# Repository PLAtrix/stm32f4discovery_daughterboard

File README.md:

This is a Daughterboard for the STM32F4 Discovery for Paparazzi.
Mainly a brakout board for all bus (UART, SPI, I2C...) and PWM outputs.

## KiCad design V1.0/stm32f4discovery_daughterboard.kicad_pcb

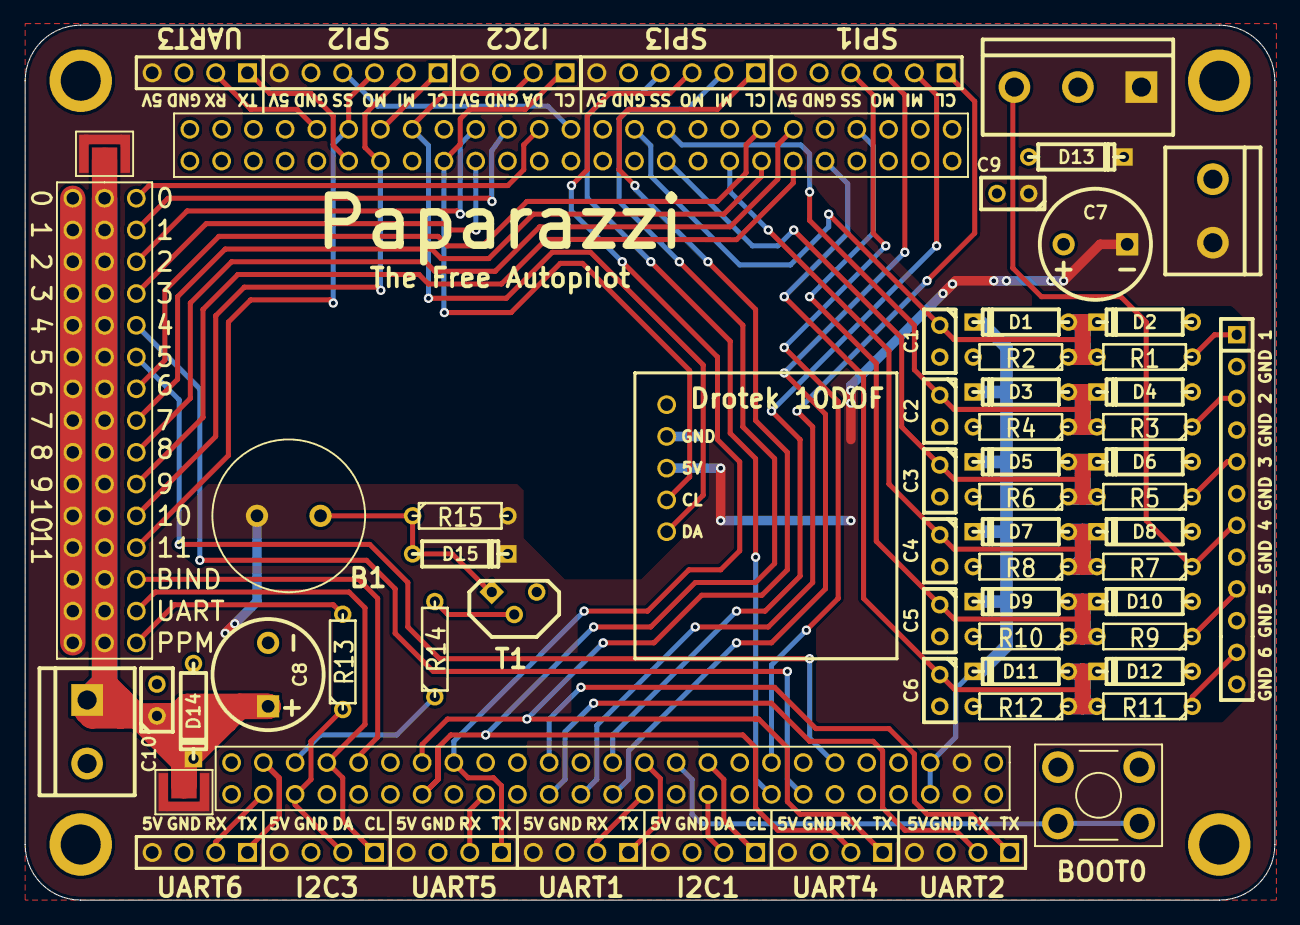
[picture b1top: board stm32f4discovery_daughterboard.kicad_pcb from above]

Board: 2 copper layers, 99.9 x 70.0 mm, 69 parts (0 on the bottom side), 60 nets.

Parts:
3,2mm1, 3,2mm2, 3,2mm3, 3,2mm4: MOUNTING_HOLE; mounting_hole_3,2mm
ADC1: CONN_12; SIL-12
B1: BUZZER_12.2X3.5; buzzer_PS1240P02CT3
BOOT0: SW_PUSH; pushbutton_tactile
C1, C2, C3, C4, C5, C6, C9, C10: 100n; C1
C7, C8: CAPAPOL; C2V8
D1, D2, D3, D4, D5, D6, D7, D8, D9, D10, D11, D12, D13, D14, D15: DIODE; D3
Drotek10DOF1: CONN_5; drotek10dof
I2C1, I2C2, I2C3: CONN_4; PIN_ARRAY_4x1
JP1, JP2: JUMPER; Ujumper
P1, P2: CONN_25X2; pin_array_25x2
PWM/PPM/Spektrum1: CONN_15X3; pin_array_15x3
R1, R3, R5, R7, R9, R11: 22k; R3
R2, R4, R6, R8, R10, R12: 2k2; R3
R13: 220; R3
R14: 470; R3
R15: 1k; R3
SPI1, SPI2, SPI3: CONN_6; PIN_ARRAY-6X1
T1: BC547; TO92
UART1, UART2, UART3, UART4, UART5, UART6: CONN_4; PIN_ARRAY_4x1
screw1: CONN_3; bornier3
screw2, screw3: CONN_2; bornier2

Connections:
3V: D1.2, D3.2, D5.2, D7.2, D9.2, D11.2, P2.5, P2.6
5V: B1.1, C7.1, C9.1, D13.2, D15.2, Drotek10DOF1.3, I2C1.4, I2C2.4, I2C3.4, JP1.1, JP2.1, P2.3, P2.4, R15.2, SPI1.6, SPI2.6, SPI3.6, UART1.4, UART2.4, UART3.4, UART4.4, UART5.4, UART6.4, screw1.1, screw2.1
ADC1: ADC1.1, R1.1
ADC2: ADC1.3, R3.1
ADC3: ADC1.5, R5.1
ADC4: ADC1.7, R7.1, screw1.3
ADC5: ADC1.9, R9.1
ADC6: ADC1.11, R11.1
BOOT0: BOOT0.2, P2.21
GND: 3,2mm1.1, 3,2mm2.1, 3,2mm3.1, 3,2mm4.1, ADC1.2, ADC1.4, ADC1.6, ADC1.8, ADC1.10, ADC1.12, BOOT0.1, C1.2, C2.2, C3.2, C4.2, C5.2, C6.2, C7.2, C8.2, C9.2, C10.2, D2.1, D4.1, D6.1, D8.1, D10.1, D12.1, D13.1, D14.1, Drotek10DOF1.2, I2C1.3, I2C2.3, I2C3.3, P1.1, P1.2, P1.5, P1.23, P1.49, P1.50, P2.1, P2.2, P2.49, P2.50, PWM/PPM/Spektrum1.1, PWM/PPM/Spektrum1.4, PWM/PPM/Spektrum1.7, PWM/PPM/Spektrum1.10, PWM/PPM/Spektrum1.13, PWM/PPM/Spektrum1.16, PWM/PPM/Spektrum1.19, PWM/PPM/Spektrum1.22, PWM/PPM/Spektrum1.25, PWM/PPM/Spektrum1.28, PWM/PPM/Spektrum1.31, PWM/PPM/Spektrum1.34, PWM/PPM/Spektrum1.37, PWM/PPM/Spektrum1.40, PWM/PPM/Spektrum1.43, R2.2, R4.2, R6.2, R8.2, R10.2, R12.2, SPI1.5, SPI2.5, SPI3.5, T1.3, UART1.3, UART2.3, UART3.3, UART4.3, UART5.3, UART6.3, screw1.2, screw2.2, screw3.2
unnamed: R14.2, T1.2
unnamed: PWM/PPM/Spektrum1.45, R13.2
unnamed: B1.2, D15.1, R15.1, T1.1
PA0: P1.12, PWM/PPM/Spektrum1.30
PA1: P1.11, PWM/PPM/Spektrum1.27
PA2: P1.14, PWM/PPM/Spektrum1.24
PA3: P1.13, PWM/PPM/Spektrum1.21
PA4: C4.1, D7.1, D8.2, P1.16, R7.2, R8.1
PA8: I2C3.1, P2.43, PWM/PPM/Spektrum1.42
PA10: P2.41, PWM/PPM/Spektrum1.39
PB1: C1.1, D1.1, D2.2, P1.21, R1.2, R2.1
PB3: P2.28, SPI1.1
PB4: P2.25, SPI1.2
PB5: P2.26, SPI1.3
PB6: P2.23, UART1.1
PB7: P2.24, UART1.2
PB8: I2C1.1, P2.19
PB9: I2C1.2, P2.20
PB10: Drotek10DOF1.4, I2C2.1, P1.34
PB11: Drotek10DOF1.5, I2C2.2, P1.35
PB13: P1.37, SPI2.1
PB14: P1.38, PWM/PPM/Spektrum1.33, SPI2.2
PB15: P1.39, PWM/PPM/Spektrum1.36, SPI2.3
PC1: C5.1, D9.1, D10.2, P1.7, R9.2, R10.1
PC2: C6.1, D11.1, D12.2, P1.10, R11.2, R12.1
PC4: C3.1, D5.1, D6.2, P1.20, R5.2, R6.1
PC5: C2.1, D3.1, D4.2, P1.19, R3.2, R4.1
PC6: P2.47, UART6.1
PC7: P2.48, UART6.2
PC8: P2.45, R14.1
PC9: I2C3.2, P2.46, R13.1
PC10: P2.37, SPI3.1, UART4.1
PC11: P2.38, SPI3.2, UART4.2
PC12: P2.35, SPI3.3, UART5.1
PD2: P2.34, UART5.2
PD5: P2.29, UART2.1
PD6: P2.30, UART2.2
PD8: P1.40, UART3.1
PD9: P1.41, UART3.2
PE2: P2.15, SPI1.4
PE3: P2.16, SPI3.4
PE5: P2.14, PWM/PPM/Spektrum1.15
PE6: P2.11, PWM/PPM/Spektrum1.18
PE7: P1.25, SPI2.4
PE9: P1.27, PWM/PPM/Spektrum1.3
PE11: P1.29, PWM/PPM/Spektrum1.6
PE13: P1.31, PWM/PPM/Spektrum1.9
PE14: P1.32, PWM/PPM/Spektrum1.12
PWM_VIN: C8.1, C10.1, D14.2, JP1.2, JP2.2, PWM/PPM/Spektrum1.2, PWM/PPM/Spektrum1.5, PWM/PPM/Spektrum1.8, PWM/PPM/Spektrum1.11, PWM/PPM/Spektrum1.14, PWM/PPM/Spektrum1.17, PWM/PPM/Spektrum1.20, PWM/PPM/Spektrum1.23, PWM/PPM/Spektrum1.26, PWM/PPM/Spektrum1.29, PWM/PPM/Spektrum1.32, PWM/PPM/Spektrum1.35, PWM/PPM/Spektrum1.38, PWM/PPM/Spektrum1.41, PWM/PPM/Spektrum1.44, screw3.1
VDD: P1.3, P1.4, P2.22

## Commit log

2014-03-13 initial push
2014-03-13 small improvements
2014-03-14 added v1 to name
2014-03-15 added version 2
2014-03-16 updated v2
2014-03-16 sikscreen
    sikscreen, paparazzi logo, prototyping are
2014-03-17 replaced v1 with v2
    deleted v1, renamed v2 to v1
2014-03-17 small changes
2014-03-17 minor edit
2014-03-17 corrected adc voltage divider
2014-03-18 added suppressor diode on all adc
2014-03-19 added tht version (without suppressor diodes)
2014-03-19 all tht components, adc input protection with diodes
2014-03-20 input protection
2014-03-22 deleted old version, small changes in tht version
2014-03-22 minor edits
2014-04-02 changed to kicad
2014-04-02 added pdf
2014-04-03 added gerber
    only first version, cleanup is required
2014-04-03 added pdf
    wrong trace with on pdf !
2014-04-07 added filter caps on input
2014-04-11 final v1.0
